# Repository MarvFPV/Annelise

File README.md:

# Annelise
A PrimeE-Style gasket mounted 3d printable keyboard

!!Warning: Will not fit original PrimeE PCB!!

I have so far only printed one case, still waiting for plate. 
As this is basically an untested keyboard at this point, i have only released the f3z archive file for now. 
Feel free to tinker around, also, enable "component colour cycling", makes the timeline and whole project much nicer to work with.

More progess to this project will hopefully follow shortly.

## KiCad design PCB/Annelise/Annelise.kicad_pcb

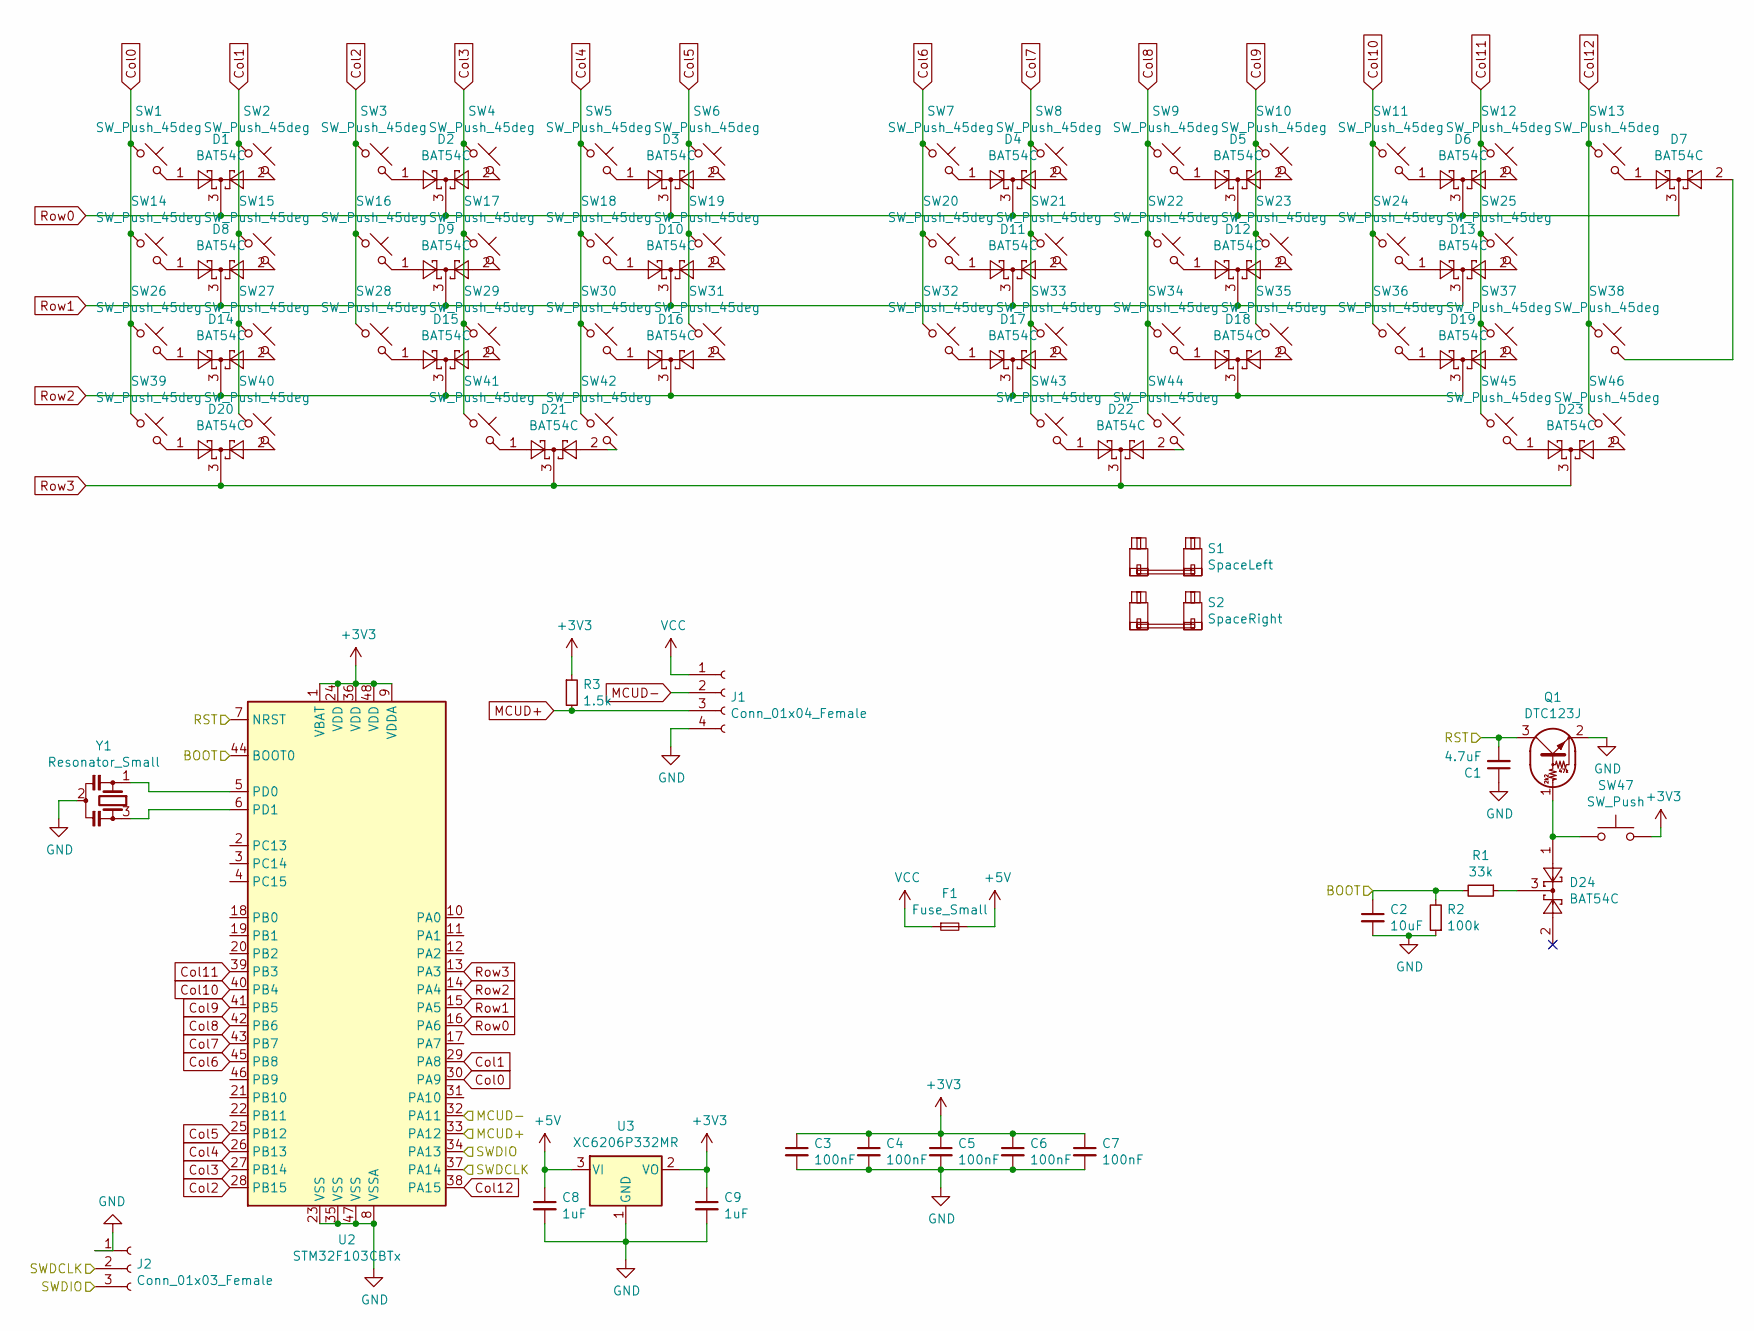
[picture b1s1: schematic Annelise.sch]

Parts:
C1: 4.7uF; C_0603_1608Metric
C2: 10uF; C_0603_1608Metric
C3, C4, C5, C6, C7: 100nF; C_0603_1608Metric
C8, C9: 1uF; C_0603_1608Metric
D1, D2, D3, D4, D5, D6, D7, D8, D9, D10, D11, D12, D13, D14, D15, D16, D17, D18, D19, D20, D21, D22, D23, D24: BAT54C; SOT-23
F1: Fuse_Small; Fuse_1206_3216Metric
J1: Conn_01x04_Female; JST_SH_SM04B-SRSS-TB_1x04-1MP_P1.00mm_Horizontal
J2: Conn_01x03_Female; PinHeader_1x03_P2.54mm_Vertical
Q1: DTC123J; SOT-23
R1: 33k; R_0603_1608Metric
R2: 100k; R_0603_1608Metric
R3: 1.5k; R_0603_1608Metric
S1: SpaceLeft; STAB_MX_2u
S2: SpaceRight; STAB_MX_2.25u
SW1, SW2, SW3, SW4, SW5, SW6, SW7, SW8, SW9, SW10, SW11, SW12, SW13, SW15, SW16, SW17, SW18, SW19, SW20, SW21, SW22, SW23, SW24, SW27, SW28, SW29, SW30, SW31, SW32, SW33, SW34, SW35, SW36, SW37, SW42, SW43: SW_Push_45deg; SW_MX_1u
SW14, SW38, SW39, SW40, SW41, SW44, SW45, SW46: SW_Push_45deg; SW_MX_1.25u
SW25, SW26: SW_Push_45deg; SW_MX_1.75u
SW47: SW_Push; PinHeader_1x02_P1.27mm_Vertical
U2: STM32F103CBTx; LQFP-48_7x7mm_P0.5mm
U3: XC6206P332MR; SOT-23
Y1: Resonator_Small; Resonator_SMD_muRata_CSTxExxV-3Pin_3.0x1.1mm

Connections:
+3V3: C3.1, C4.1, C5.1, C6.1, C7.1, C9.1, R3.1, SW47.2, U2.1 (VBAT), U2.9 (VDDA), U2.24 (VDD), U2.36 (VDD), U2.48 (VDD), U3.2 (VO); also elsewhere on the board
+5V: C8.1, F1.2, U3.3 (VI)
/BOOT: C2.1, R1.2, R2.2, U2.44 (BOOT0)
/RST: C1.2, Q1.3 (C), U2.7 (NRST)
/SWDCLK: J2.2, U2.37 (PA14); also elsewhere on the board
/SWDIO: J2.3, U2.34 (PA13); also elsewhere on the board
Col0: SW1.1, SW14.1, SW26.1, SW39.1, U2.30 (PA9)
Col1: SW2.1, SW15.1, SW27.1, SW40.1, U2.29 (PA8)
Col2: SW3.1, SW16.1, SW28.1, U2.28 (PB15)
Col3: SW4.1, SW17.1, SW29.1, SW41.1, U2.27 (PB14)
Col4: SW5.1, SW18.1, SW30.1, SW42.1, U2.26 (PB13)
Col5: SW6.1, SW19.1, SW31.1, U2.25 (PB12)
Col6: SW7.1, SW20.1, SW32.1, U2.45 (PB8)
Col7: SW8.1, SW21.1, SW33.1, SW43.1, U2.43 (PB7)
Col8: SW9.1, SW22.1, SW34.1, SW44.1, U2.42 (PB6)
Col9: SW10.1, SW23.1, SW35.1, U2.41 (PB5)
Col10: SW11.1, SW24.1, SW36.1, U2.40 (PB4)
Col11: SW12.1, SW25.1, SW37.1, SW45.1, U2.39 (PB3)
Col12: SW13.1, SW38.1, SW46.1, U2.38 (PA15)
GND: C1.1, C2.2, C3.2, C4.2, C5.2, C6.2, C7.2, C8.2, C9.2, J1.4, J2.1, Q1.2 (E), R2.1, U2.8 (VSSA), U2.23 (VSS), U2.35 (VSS), U2.47 (VSS), U3.1 (GND), Y1.2; also elsewhere on the board
MCUD+: J1.3, R3.2, U2.33 (PA12)
MCUD-: J1.2, U2.32 (PA11)
unnamed: D1.1, SW1.2
unnamed: D1.2, SW2.2
unnamed: D2.1, SW3.2
unnamed: D2.2, SW4.2
unnamed: D3.1, SW5.2
unnamed: D3.2, SW6.2
unnamed: D4.1, SW7.2
unnamed: D4.2, SW8.2
unnamed: D5.1, SW9.2
unnamed: D5.2, SW10.2
unnamed: D6.1, SW11.2
unnamed: D6.2, SW12.2
unnamed: D7.1, SW13.2
unnamed: D7.2, SW38.2
unnamed: D8.1, SW14.2
unnamed: D8.2, SW15.2
unnamed: D9.1, SW16.2
unnamed: D9.2, SW17.2
unnamed: D10.1, SW18.2
unnamed: D10.2, SW19.2
unnamed: D11.1, SW20.2
unnamed: D11.2, SW21.2
unnamed: D12.1, SW22.2
unnamed: D12.2, SW23.2
unnamed: D13.1, SW24.2
unnamed: D13.2, SW25.2
unnamed: D14.1, SW26.2
unnamed: D14.2, SW27.2
unnamed: D15.1, SW28.2
unnamed: D15.2, SW29.2
unnamed: D16.1, SW30.2
unnamed: D16.2, SW31.2
unnamed: D17.1, SW32.2
unnamed: D17.2, SW33.2
unnamed: D18.1, SW34.2
unnamed: D18.2, SW35.2
unnamed: D19.1, SW36.2
unnamed: D19.2, SW37.2
unnamed: D20.1, SW39.2
unnamed: D20.2, SW40.2
unnamed: D21.1, SW41.2
unnamed: D21.2, SW42.2
unnamed: D22.1, SW43.2
unnamed: D22.2, SW44.2
unnamed: D23.1, SW45.2
unnamed: D23.2, SW46.2
unnamed 68: D24.1, Q1.1 (B), SW47.1; also elsewhere on the board
unnamed: D24.3, R1.1
unnamed: U2.5 (PD0), Y1.1
unnamed: U2.6 (PD1), Y1.3
Row0: D1.3, D2.3, D3.3, D4.3, D5.3, D6.3, D7.3, U2.16 (PA6)
Row1: D8.3, D9.3, D10.3, D11.3, D12.3, D13.3, U2.15 (PA5)
Row2: D14.3, D15.3, D16.3, D17.3, D18.3, D19.3, U2.14 (PA4)
Row3: D20.3, D21.3, D22.3, D23.3, U2.13 (PA3)
VCC: F1.1, J1.1

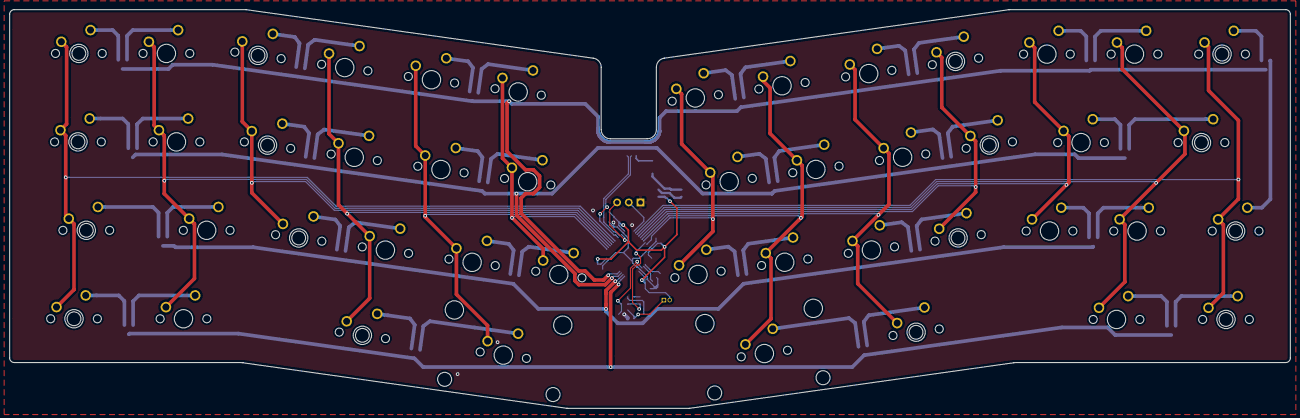
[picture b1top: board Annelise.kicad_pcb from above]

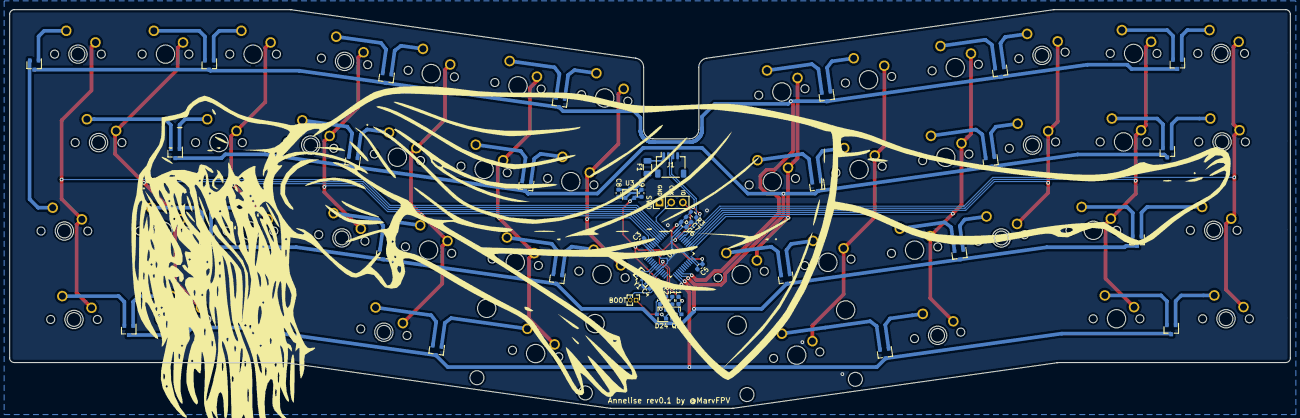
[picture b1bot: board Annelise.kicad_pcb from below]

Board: 2 copper layers, 278.6 x 86.7 mm, 92 parts (44 on the bottom side), 77 nets.

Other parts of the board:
BOOT: SW_Push; PinHeader_1x02_P1.27mm_Vertical
SWD: Conn_01x03_Female; PinHeader_1x03_P2.54mm_Vertical

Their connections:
+3V3: BOOT.2; also elsewhere on the board
/SWDCLK: SWD.2; also elsewhere on the board
/SWDIO: SWD.3; also elsewhere on the board
GND: SWD.1; also elsewhere on the board
unnamed 68: BOOT.1; also elsewhere on the board

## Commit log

2021-05-04 pcb started
2021-05-04 pcb updates
2021-06-08 Updated . f3z
